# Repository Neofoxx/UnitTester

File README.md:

# UnitTester
A rack mounted piece of gear for testing chips

#### Why
Always wanted some rack-mount piece of gear based on the DIN 41612 standard. This is slightly modified.
Also, want to test the complete PIC32 toolchain without plugging and replugging the programmer a thousand times.

#### When
Soon.

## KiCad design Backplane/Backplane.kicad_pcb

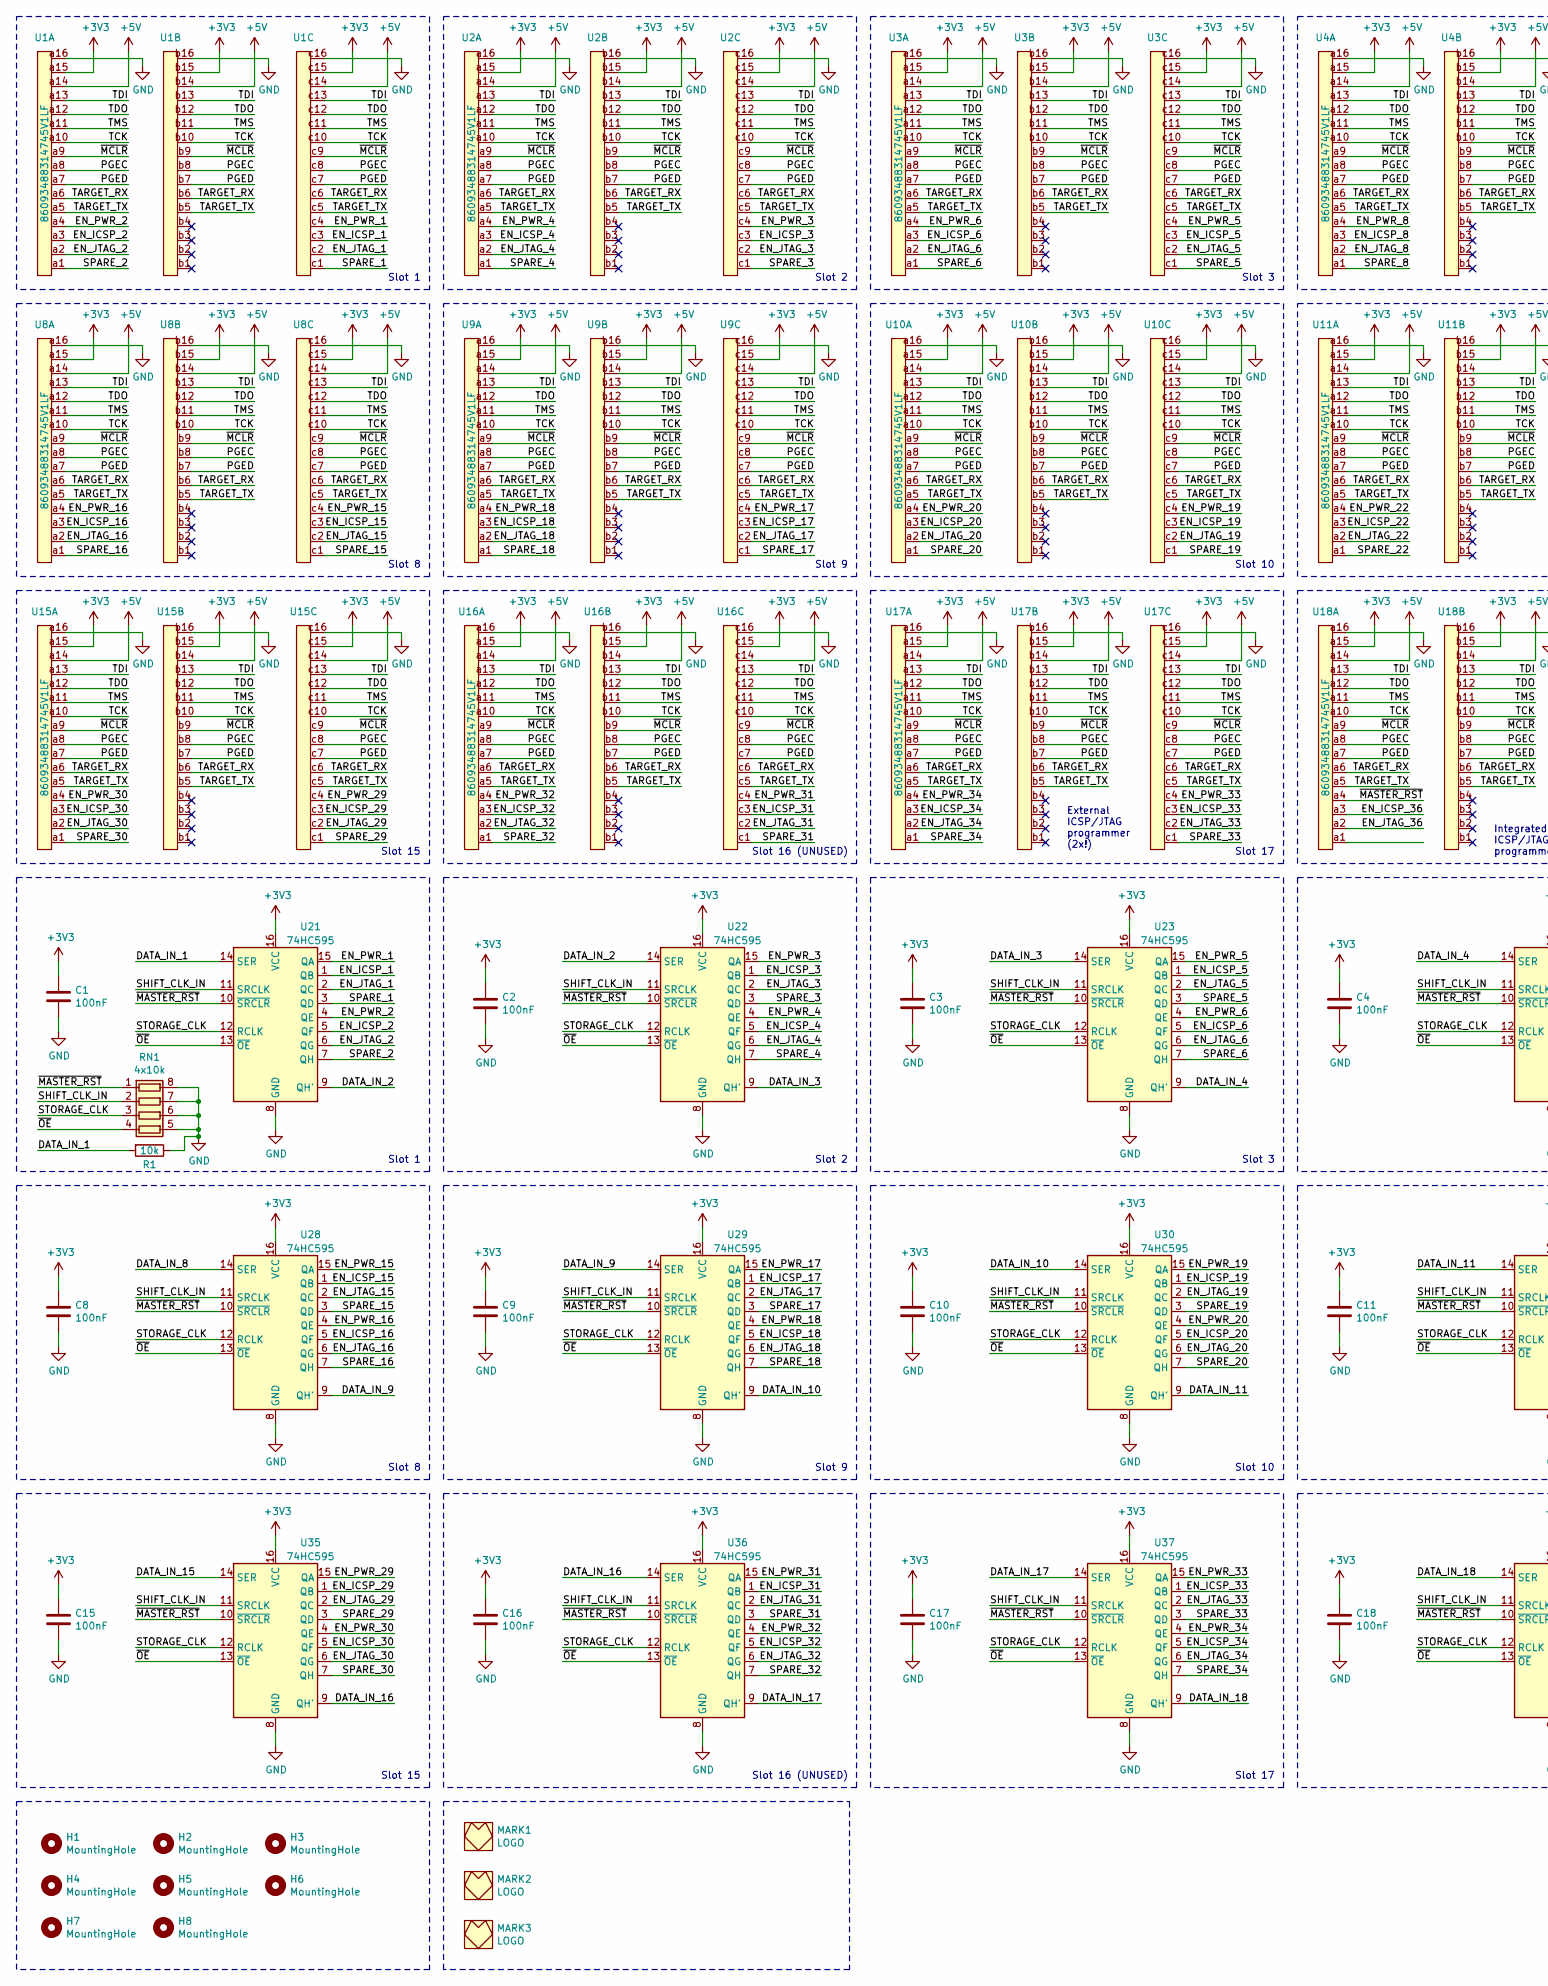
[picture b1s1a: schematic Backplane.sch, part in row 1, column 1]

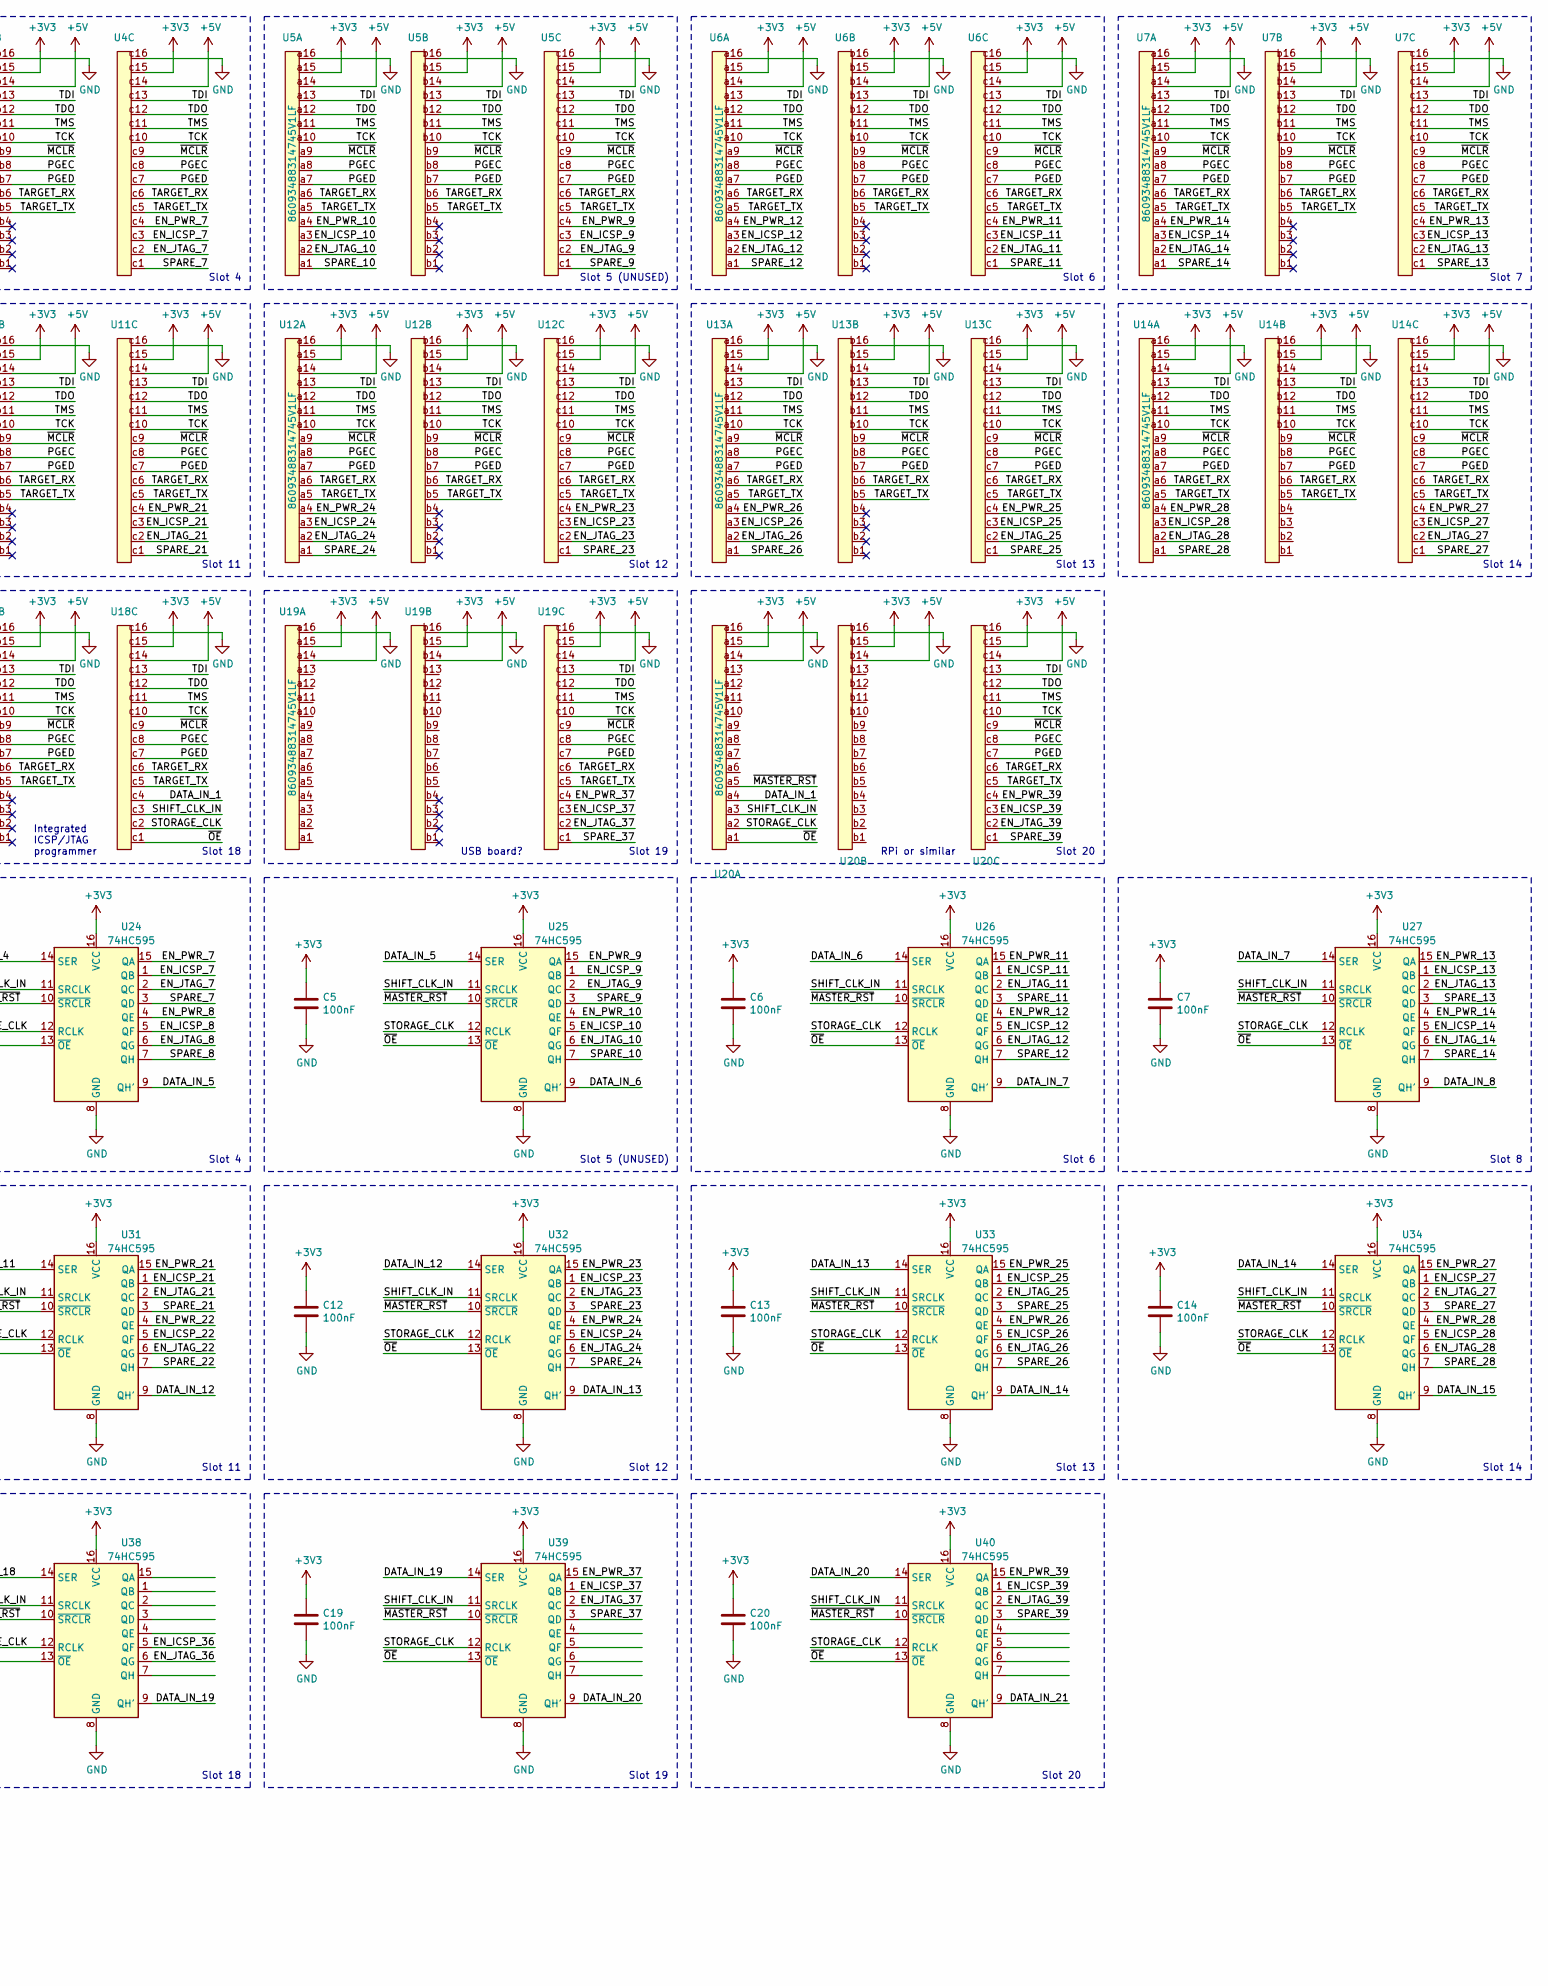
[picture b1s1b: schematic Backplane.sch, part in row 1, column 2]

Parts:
C1, C2, C3, C4, C5, C6, C7, C8, C9, C10, C11, C12, C13, C14, C15, C16, C17, C18, C19, C20: 100nF; C_0603_1608Metric_Pad1.08x0.95mm_HandSolder
H1, H2, H3, H4, H5, H6, H7, H8: MountingHole; MountingHole_3.2mm_M3
MARK1: LOGO; FOX_LOGO_COPPER
MARK2: LOGO; FOX_LOGO_MASK
MARK3: LOGO; FOX_LOGO_SILK
R1: 10k; R_0603_1608Metric_Pad0.98x0.95mm_HandSolder
RN1: 4x10k; R_Array_Convex_4x0603
U1, U2, U3, U4, U5, U6, U7, U8, U9, U10, U11, U12, U13, U14, U15, U16, U17, U18, U19, U20: 86093488314745V1LF; DIN41612_C2_3x16_Female_Vertical_THT; Mouser 649-869348314745V1LF
U21, U22, U23, U24, U25, U26, U27, U28, U29, U30, U31, U32, U33, U34, U35, U36, U37, U38, U39, U40: 74HC595; TSSOP-16_4.4x5mm_P0.65mm

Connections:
+3V3: C1.1, C2.1, C3.1, C4.1, C5.1, C6.1, C7.1, C8.1, C9.1, C10.1, C11.1, C12.1, C13.1, C14.1, C15.1, C16.1, C17.1, C18.1, C19.1, C20.1, U1.a15, U1.b15, U1.c15, U2.a15, U2.b15, U2.c15, U3.a15, U3.b15, U3.c15, U4.a15, U4.b15, U4.c15, U5.a15, U5.b15, U5.c15, U6.a15, U6.b15, U6.c15, U7.a15, U7.b15, U7.c15, U8.a15, U8.b15, U8.c15, U9.a15, U9.b15, U9.c15, U10.a15, U10.b15, U10.c15, U11.a15, U11.b15, U11.c15, U12.a15, U12.b15, U12.c15, U13.a15, U13.b15, U13.c15, U14.a15, U14.b15, U14.c15, U15.a15, U15.b15, U15.c15, U16.a15, U16.b15, U16.c15, U17.a15, U17.b15, U17.c15, U18.a15, U18.b15, U18.c15, U19.a15, U19.b15, U19.c15, U20.a15, U20.b15, U20.c15, U21.16 (VCC), U22.16 (VCC), U23.16 (VCC), U24.16 (VCC), U25.16 (VCC), U26.16 (VCC), U27.16 (VCC), U28.16 (VCC), U29.16 (VCC), U30.16 (VCC), U31.16 (VCC), U32.16 (VCC), U33.16 (VCC), U34.16 (VCC), U35.16 (VCC), U36.16 (VCC), U37.16 (VCC), U38.16 (VCC), U39.16 (VCC), U40.16 (VCC)
+5V: U1.a14, U1.b14, U1.c14, U2.a14, U2.b14, U2.c14, U3.a14, U3.b14, U3.c14, U4.a14, U4.b14, U4.c14, U5.a14, U5.b14, U5.c14, U6.a14, U6.b14, U6.c14, U7.a14, U7.b14, U7.c14, U8.a14, U8.b14, U8.c14, U9.a14, U9.b14, U9.c14, U10.a14, U10.b14, U10.c14, U11.a14, U11.b14, U11.c14, U12.a14, U12.b14, U12.c14, U13.a14, U13.b14, U13.c14, U14.a14, U14.b14, U14.c14, U15.a14, U15.b14, U15.c14, U16.a14, U16.b14, U16.c14, U17.a14, U17.b14, U17.c14, U18.a14, U18.b14, U18.c14, U19.a14, U19.b14, U19.c14, U20.a14, U20.b14, U20.c14
/DATA_IN_1: R1.2, U18.c4, U20.a4, U21.14 (SER)
/DATA_IN_2: U21.9 (QH'), U22.14 (SER)
/DATA_IN_3: U22.9 (QH'), U23.14 (SER)
/DATA_IN_4: U23.9 (QH'), U24.14 (SER)
/DATA_IN_5: U24.9 (QH'), U25.14 (SER)
/DATA_IN_6: U25.9 (QH'), U26.14 (SER)
/DATA_IN_7: U26.9 (QH'), U27.14 (SER)
/DATA_IN_8: U27.9 (QH'), U28.14 (SER)
/DATA_IN_9: U28.9 (QH'), U29.14 (SER)
/DATA_IN_10: U29.9 (QH'), U30.14 (SER)
/DATA_IN_11: U30.9 (QH'), U31.14 (SER)
/DATA_IN_12: U31.9 (QH'), U32.14 (SER)
/DATA_IN_13: U32.9 (QH'), U33.14 (SER)
/DATA_IN_14: U33.9 (QH'), U34.14 (SER)
/DATA_IN_15: U34.9 (QH'), U35.14 (SER)
/DATA_IN_16: U35.9 (QH'), U36.14 (SER)
/DATA_IN_17: U36.9 (QH'), U37.14 (SER)
/DATA_IN_18: U37.9 (QH'), U38.14 (SER)
/DATA_IN_19: U38.9 (QH'), U39.14 (SER)
/DATA_IN_20: U39.9 (QH'), U40.14 (SER)
/EN_ICSP_1: U1.c3, U21.1 (QB)
/EN_ICSP_2: U1.a3, U21.5 (QF)
/EN_ICSP_3: U2.c3, U22.1 (QB)
/EN_ICSP_4: U2.a3, U22.5 (QF)
/EN_ICSP_5: U3.c3, U23.1 (QB)
/EN_ICSP_6: U3.a3, U23.5 (QF)
/EN_ICSP_7: U4.c3, U24.1 (QB)
/EN_ICSP_8: U4.a3, U24.5 (QF)
/EN_ICSP_9: U5.c3, U25.1 (QB)
/EN_ICSP_10: U5.a3, U25.5 (QF)
/EN_ICSP_11: U6.c3, U26.1 (QB)
/EN_ICSP_12: U6.a3, U26.5 (QF)
/EN_ICSP_13: U7.c3, U27.1 (QB)
/EN_ICSP_14: U7.a3, U27.5 (QF)
/EN_ICSP_15: U8.c3, U28.1 (QB)
/EN_ICSP_16: U8.a3, U28.5 (QF)
/EN_ICSP_17: U9.c3, U29.1 (QB)
/EN_ICSP_18: U9.a3, U29.5 (QF)
/EN_ICSP_19: U10.c3, U30.1 (QB)
/EN_ICSP_20: U10.a3, U30.5 (QF)
/EN_ICSP_21: U11.c3, U31.1 (QB)
/EN_ICSP_22: U11.a3, U31.5 (QF)
/EN_ICSP_23: U12.c3, U32.1 (QB)
/EN_ICSP_24: U12.a3, U32.5 (QF)
/EN_ICSP_25: U13.c3, U33.1 (QB)
/EN_ICSP_26: U13.a3, U33.5 (QF)
/EN_ICSP_27: U14.c3, U34.1 (QB)
/EN_ICSP_28: U14.a3, U34.5 (QF)
/EN_ICSP_29: U15.c3, U35.1 (QB)
/EN_ICSP_30: U15.a3, U35.5 (QF)
/EN_ICSP_31: U16.c3, U36.1 (QB)
/EN_ICSP_32: U16.a3, U36.5 (QF)
/EN_ICSP_33: U17.c3, U37.1 (QB)
/EN_ICSP_34: U17.a3, U37.5 (QF)
/EN_ICSP_36: U18.a3, U38.5 (QF)
/EN_ICSP_37: U19.c3, U39.1 (QB)
/EN_ICSP_39: U20.c3, U40.1 (QB)
/EN_JTAG_1: U1.c2, U21.2 (QC)
/EN_JTAG_2: U1.a2, U21.6 (QG)
/EN_JTAG_3: U2.c2, U22.2 (QC)
/EN_JTAG_4: U2.a2, U22.6 (QG)
/EN_JTAG_5: U3.c2, U23.2 (QC)
/EN_JTAG_6: U3.a2, U23.6 (QG)
/EN_JTAG_7: U4.c2, U24.2 (QC)
/EN_JTAG_8: U4.a2, U24.6 (QG)
/EN_JTAG_9: U5.c2, U25.2 (QC)
/EN_JTAG_10: U5.a2, U25.6 (QG)
/EN_JTAG_11: U6.c2, U26.2 (QC)
/EN_JTAG_12: U6.a2, U26.6 (QG)
/EN_JTAG_13: U7.c2, U27.2 (QC)
/EN_JTAG_14: U7.a2, U27.6 (QG)
/EN_JTAG_15: U8.c2, U28.2 (QC)
/EN_JTAG_16: U8.a2, U28.6 (QG)
/EN_JTAG_17: U9.c2, U29.2 (QC)
/EN_JTAG_18: U9.a2, U29.6 (QG)
/EN_JTAG_19: U10.c2, U30.2 (QC)
/EN_JTAG_20: U10.a2, U30.6 (QG)
/EN_JTAG_21: U11.c2, U31.2 (QC)
/EN_JTAG_22: U11.a2, U31.6 (QG)
/EN_JTAG_23: U12.c2, U32.2 (QC)
/EN_JTAG_24: U12.a2, U32.6 (QG)
/EN_JTAG_25: U13.c2, U33.2 (QC)
/EN_JTAG_26: U13.a2, U33.6 (QG)
/EN_JTAG_27: U14.c2, U34.2 (QC)
/EN_JTAG_28: U14.a2, U34.6 (QG)
/EN_JTAG_29: U15.c2, U35.2 (QC)
/EN_JTAG_30: U15.a2, U35.6 (QG)
/EN_JTAG_31: U16.c2, U36.2 (QC)
/EN_JTAG_32: U16.a2, U36.6 (QG)
/EN_JTAG_33: U17.c2, U37.2 (QC)
/EN_JTAG_34: U17.a2, U37.6 (QG)
/EN_JTAG_36: U18.a2, U38.6 (QG)
/EN_JTAG_37: U19.c2, U39.2 (QC)
/EN_JTAG_39: U20.c2, U40.2 (QC)
/EN_PWR_1: U1.c4, U21.15 (QA)
/EN_PWR_2: U1.a4, U21.4 (QE)
/EN_PWR_3: U2.c4, U22.15 (QA)
/EN_PWR_4: U2.a4, U22.4 (QE)
/EN_PWR_5: U3.c4, U23.15 (QA)
/EN_PWR_6: U3.a4, U23.4 (QE)
/EN_PWR_7: U4.c4, U24.15 (QA)
/EN_PWR_8: U4.a4, U24.4 (QE)
/EN_PWR_9: U5.c4, U25.15 (QA)
/EN_PWR_10: U5.a4, U25.4 (QE)
/EN_PWR_11: U6.c4, U26.15 (QA)
/EN_PWR_12: U6.a4, U26.4 (QE)
/EN_PWR_13: U7.c4, U27.15 (QA)
/EN_PWR_14: U7.a4, U27.4 (QE)
/EN_PWR_15: U8.c4, U28.15 (QA)
/EN_PWR_16: U8.a4, U28.4 (QE)
/EN_PWR_17: U9.c4, U29.15 (QA)
/EN_PWR_18: U9.a4, U29.4 (QE)
/EN_PWR_19: U10.c4, U30.15 (QA)
/EN_PWR_20: U10.a4, U30.4 (QE)
/EN_PWR_21: U11.c4, U31.15 (QA)
/EN_PWR_22: U11.a4, U31.4 (QE)
/EN_PWR_23: U12.c4, U32.15 (QA)
/EN_PWR_24: U12.a4, U32.4 (QE)
/EN_PWR_25: U13.c4, U33.15 (QA)
/EN_PWR_26: U13.a4, U33.4 (QE)
/EN_PWR_27: U14.c4, U34.15 (QA)
/EN_PWR_28: U14.a4, U34.4 (QE)
/EN_PWR_29: U15.c4, U35.15 (QA)
/EN_PWR_30: U15.a4, U35.4 (QE)
/EN_PWR_31: U16.c4, U36.15 (QA)
/EN_PWR_32: U16.a4, U36.4 (QE)
/EN_PWR_33: U17.c4, U37.15 (QA)
/EN_PWR_34: U17.a4, U37.4 (QE)
/EN_PWR_37: U19.c4, U39.15 (QA)
/EN_PWR_39: U20.c4, U40.15 (QA)
/PGEC: U1.a8, U1.b8, U1.c8, U2.a8, U2.b8, U2.c8, U3.a8, U3.b8, U3.c8, U4.a8, U4.b8, U4.c8, U5.a8, U5.b8, U5.c8, U6.a8, U6.b8, U6.c8, U7.a8, U7.b8, U7.c8, U8.a8, U8.b8, U8.c8, U9.a8, U9.b8, U9.c8, U10.a8, U10.b8, U10.c8, U11.a8, U11.b8, U11.c8, U12.a8, U12.b8, U12.c8, U13.a8, U13.b8, U13.c8, U14.a8, U14.b8, U14.c8, U15.a8, U15.b8, U15.c8, U16.a8, U16.b8, U16.c8, U17.a8, U17.b8, U17.c8, U18.a8, U18.b8, U18.c8, U19.c8, U20.c8
/PGED: U1.a7, U1.b7, U1.c7, U2.a7, U2.b7, U2.c7, U3.a7, U3.b7, U3.c7, U4.a7, U4.b7, U4.c7, U5.a7, U5.b7, U5.c7, U6.a7, U6.b7, U6.c7, U7.a7, U7.b7, U7.c7, U8.a7, U8.b7, U8.c7, U9.a7, U9.b7, U9.c7, U10.a7, U10.b7, U10.c7, U11.a7, U11.b7, U11.c7, U12.a7, U12.b7, U12.c7, U13.a7, U13.b7, U13.c7, U14.a7, U14.b7, U14.c7, U15.a7, U15.b7, U15.c7, U16.a7, U16.b7, U16.c7, U17.a7, U17.b7, U17.c7, U18.a7, U18.b7, U18.c7, U19.c7, U20.c7
/SHIFT_CLK_IN: RN1.2 (R2.1), U18.c3, U20.a3, U21.11 (SRCLK), U22.11 (SRCLK), U23.11 (SRCLK), U24.11 (SRCLK), U25.11 (SRCLK), U26.11 (SRCLK), U27.11 (SRCLK), U28.11 (SRCLK), U29.11 (SRCLK), U30.11 (SRCLK), U31.11 (SRCLK), U32.11 (SRCLK), U33.11 (SRCLK), U34.11 (SRCLK), U35.11 (SRCLK), U36.11 (SRCLK), U37.11 (SRCLK), U38.11 (SRCLK), U39.11 (SRCLK), U40.11 (SRCLK)
/SPARE_1: U1.c1, U21.3 (QD)
/SPARE_2: U1.a1, U21.7 (QH)
/SPARE_3: U2.c1, U22.3 (QD)
/SPARE_4: U2.a1, U22.7 (QH)
/SPARE_5: U3.c1, U23.3 (QD)
/SPARE_6: U3.a1, U23.7 (QH)
/SPARE_7: U4.c1, U24.3 (QD)
/SPARE_8: U4.a1, U24.7 (QH)
/SPARE_9: U5.c1, U25.3 (QD)
/SPARE_10: U5.a1, U25.7 (QH)
/SPARE_11: U6.c1, U26.3 (QD)
/SPARE_12: U6.a1, U26.7 (QH)
/SPARE_13: U7.c1, U27.3 (QD)
/SPARE_14: U7.a1, U27.7 (QH)
/SPARE_15: U8.c1, U28.3 (QD)
/SPARE_16: U8.a1, U28.7 (QH)
/SPARE_17: U9.c1, U29.3 (QD)
/SPARE_18: U9.a1, U29.7 (QH)
/SPARE_19: U10.c1, U30.3 (QD)
/SPARE_20: U10.a1, U30.7 (QH)
/SPARE_21: U11.c1, U31.3 (QD)
/SPARE_22: U11.a1, U31.7 (QH)
/SPARE_23: U12.c1, U32.3 (QD)
/SPARE_24: U12.a1, U32.7 (QH)
/SPARE_25: U13.c1, U33.3 (QD)
/SPARE_26: U13.a1, U33.7 (QH)
/SPARE_27: U14.c1, U34.3 (QD)
/SPARE_28: U14.a1, U34.7 (QH)
/SPARE_29: U15.c1, U35.3 (QD)
/SPARE_30: U15.a1, U35.7 (QH)
/SPARE_31: U16.c1, U36.3 (QD)
/SPARE_32: U16.a1, U36.7 (QH)
/SPARE_33: U17.c1, U37.3 (QD)
/SPARE_34: U17.a1, U37.7 (QH)
/SPARE_37: U19.c1, U39.3 (QD)
/SPARE_39: U20.c1, U40.3 (QD)
/STORAGE_CLK: RN1.3 (R3.1), U18.c2, U20.a2, U21.12 (RCLK), U22.12 (RCLK), U23.12 (RCLK), U24.12 (RCLK), U25.12 (RCLK), U26.12 (RCLK), U27.12 (RCLK), U28.12 (RCLK), U29.12 (RCLK), U30.12 (RCLK), U31.12 (RCLK), U32.12 (RCLK), U33.12 (RCLK), U34.12 (RCLK), U35.12 (RCLK), U36.12 (RCLK), U37.12 (RCLK), U38.12 (RCLK), U39.12 (RCLK), U40.12 (RCLK)
/TARGET_RX: U1.a6, U1.b6, U1.c6, U2.a6, U2.b6, U2.c6, U3.a6, U3.b6, U3.c6, U4.a6, U4.b6, U4.c6, U5.a6, U5.b6, U5.c6, U6.a6, U6.b6, U6.c6, U7.a6, U7.b6, U7.c6, U8.a6, U8.b6, U8.c6, U9.a6, U9.b6, U9.c6, U10.a6, U10.b6, U10.c6, U11.a6, U11.b6, U11.c6, U12.a6, U12.b6, U12.c6, U13.a6, U13.b6, U13.c6, U14.a6, U14.b6, U14.c6, U15.a6, U15.b6, U15.c6, U16.a6, U16.b6, U16.c6, U17.a6, U17.b6, U17.c6, U18.a6, U18.b6, U18.c6, U19.c6, U20.c6
/TARGET_TX: U1.a5, U1.b5, U1.c5, U2.a5, U2.b5, U2.c5, U3.a5, U3.b5, U3.c5, U4.a5, U4.b5, U4.c5, U5.a5, U5.b5, U5.c5, U6.a5, U6.b5, U6.c5, U7.a5, U7.b5, U7.c5, U8.a5, U8.b5, U8.c5, U9.a5, U9.b5, U9.c5, U10.a5, U10.b5, U10.c5, U11.a5, U11.b5, U11.c5, U12.a5, U12.b5, U12.c5, U13.a5, U13.b5, U13.c5, U14.a5, U14.b5, U14.c5, U15.a5, U15.b5, U15.c5, U16.a5, U16.b5, U16.c5, U17.a5, U17.b5, U17.c5, U18.a5, U18.b5, U18.c5, U19.c5, U20.c5
/TCK: U1.a10, U1.b10, U1.c10, U2.a10, U2.b10, U2.c10, U3.a10, U3.b10, U3.c10, U4.a10, U4.b10, U4.c10, U5.a10, U5.b10, U5.c10, U6.a10, U6.b10, U6.c10, U7.a10, U7.b10, U7.c10, U8.a10, U8.b10, U8.c10, U9.a10, U9.b10, U9.c10, U10.a10, U10.b10, U10.c10, U11.a10, U11.b10, U11.c10, U12.a10, U12.b10, U12.c10, U13.a10, U13.b10, U13.c10, U14.a10, U14.b10, U14.c10, U15.a10, U15.b10, U15.c10, U16.a10, U16.b10, U16.c10, U17.a10, U17.b10, U17.c10, U18.a10, U18.b10, U18.c10, U19.c10, U20.c10
/TDI: U1.a13, U1.b13, U1.c13, U2.a13, U2.b13, U2.c13, U3.a13, U3.b13, U3.c13, U4.a13, U4.b13, U4.c13, U5.a13, U5.b13, U5.c13, U6.a13, U6.b13, U6.c13, U7.a13, U7.b13, U7.c13, U8.a13, U8.b13, U8.c13, U9.a13, U9.b13, U9.c13, U10.a13, U10.b13, U10.c13, U11.a13, U11.b13, U11.c13, U12.a13, U12.b13, U12.c13, U13.a13, U13.b13, U13.c13, U14.a13, U14.b13, U14.c13, U15.a13, U15.b13, U15.c13, U16.a13, U16.b13, U16.c13, U17.a13, U17.b13, U17.c13, U18.a13, U18.b13, U18.c13, U19.c13, U20.c13
/TDO: U1.a12, U1.b12, U1.c12, U2.a12, U2.b12, U2.c12, U3.a12, U3.b12, U3.c12, U4.a12, U4.b12, U4.c12, U5.a12, U5.b12, U5.c12, U6.a12, U6.b12, U6.c12, U7.a12, U7.b12, U7.c12, U8.a12, U8.b12, U8.c12, U9.a12, U9.b12, U9.c12, U10.a12, U10.b12, U10.c12, U11.a12, U11.b12, U11.c12, U12.a12, U12.b12, U12.c12, U13.a12, U13.b12, U13.c12, U14.a12, U14.b12, U14.c12, U15.a12, U15.b12, U15.c12, U16.a12, U16.b12, U16.c12, U17.a12, U17.b12, U17.c12, U18.a12, U18.b12, U18.c12, U19.c12, U20.c12
/TMS: U1.a11, U1.b11, U1.c11, U2.a11, U2.b11, U2.c11, U3.a11, U3.b11, U3.c11, U4.a11, U4.b11, U4.c11, U5.a11, U5.b11, U5.c11, U6.a11, U6.b11, U6.c11, U7.a11, U7.b11, U7.c11, U8.a11, U8.b11, U8.c11, U9.a11, U9.b11, U9.c11, U10.a11, U10.b11, U10.c11, U11.a11, U11.b11, U11.c11, U12.a11, U12.b11, U12.c11, U13.a11, U13.b11, U13.c11, U14.a11, U14.b11, U14.c11, U15.a11, U15.b11, U15.c11, U16.a11, U16.b11, U16.c11, U17.a11, U17.b11, U17.c11, U18.a11, U18.b11, U18.c11, U19.c11, U20.c11
/~MASTER_RST: RN1.1 (R1.1), U18.a4, U20.a5, U21.10 (~SRCLR), U22.10 (~SRCLR), U23.10 (~SRCLR), U24.10 (~SRCLR), U25.10 (~SRCLR), U26.10 (~SRCLR), U27.10 (~SRCLR), U28.10 (~SRCLR), U29.10 (~SRCLR), U30.10 (~SRCLR), U31.10 (~SRCLR), U32.10 (~SRCLR), U33.10 (~SRCLR), U34.10 (~SRCLR), U35.10 (~SRCLR), U36.10 (~SRCLR), U37.10 (~SRCLR), U38.10 (~SRCLR), U39.10 (~SRCLR), U40.10 (~SRCLR)
/~MCLR: U1.a9, U1.b9, U1.c9, U2.a9, U2.b9, U2.c9, U3.a9, U3.b9, U3.c9, U4.a9, U4.b9, U4.c9, U5.a9, U5.b9, U5.c9, U6.a9, U6.b9, U6.c9, U7.a9, U7.b9, U7.c9, U8.a9, U8.b9, U8.c9, U9.a9, U9.b9, U9.c9, U10.a9, U10.b9, U10.c9, U11.a9, U11.b9, U11.c9, U12.a9, U12.b9, U12.c9, U13.a9, U13.b9, U13.c9, U14.a9, U14.b9, U14.c9, U15.a9, U15.b9, U15.c9, U16.a9, U16.b9, U16.c9, U17.a9, U17.b9, U17.c9, U18.a9, U18.b9, U18.c9, U19.c9, U20.c9
/~OE: RN1.4 (R4.1), U18.c1, U20.a1, U21.13 (~OE), U22.13 (~OE), U23.13 (~OE), U24.13 (~OE), U25.13 (~OE), U26.13 (~OE), U27.13 (~OE), U28.13 (~OE), U29.13 (~OE), U30.13 (~OE), U31.13 (~OE), U32.13 (~OE), U33.13 (~OE), U34.13 (~OE), U35.13 (~OE), U36.13 (~OE), U37.13 (~OE), U38.13 (~OE), U39.13 (~OE), U40.13 (~OE)
GND: C1.2, C2.2, C3.2, C4.2, C5.2, C6.2, C7.2, C8.2, C9.2, C10.2, C11.2, C12.2, C13.2, C14.2, C15.2, C16.2, C17.2, C18.2, C19.2, C20.2, R1.1, RN1.5 (R4.2), RN1.6 (R3.2), RN1.7 (R2.2), RN1.8 (R1.2), U1.a16, U1.b16, U1.c16, U2.a16, U2.b16, U2.c16, U3.a16, U3.b16, U3.c16, U4.a16, U4.b16, U4.c16, U5.a16, U5.b16, U5.c16, U6.a16, U6.b16, U6.c16, U7.a16, U7.b16, U7.c16, U8.a16, U8.b16, U8.c16, U9.a16, U9.b16, U9.c16, U10.a16, U10.b16, U10.c16, U11.a16, U11.b16, U11.c16, U12.a16, U12.b16, U12.c16, U13.a16, U13.b16, U13.c16, U14.a16, U14.b16, U14.c16, U15.a16, U15.b16, U15.c16, U16.a16, U16.b16, U16.c16, U17.a16, U17.b16, U17.c16, U18.a16, U18.b16, U18.c16, U19.a16, U19.b16, U19.c16, U20.a16, U20.b16, U20.c16, U21.8 (GND), U22.8 (GND), U23.8 (GND), U24.8 (GND), U25.8 (GND), U26.8 (GND), U27.8 (GND), U28.8 (GND), U29.8 (GND), U30.8 (GND), U31.8 (GND), U32.8 (GND), U33.8 (GND), U34.8 (GND), U35.8 (GND), U36.8 (GND), U37.8 (GND), U38.8 (GND), U39.8 (GND), U40.8 (GND)

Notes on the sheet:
Slot 1
Slot 2
Slot 3
Slot 4
Slot 5 (UNUSED)
Slot 6
Slot 7
Slot 8
Slot 9
Slot 10
Slot 11
Slot 12
Slot 13
Slot 14
Slot 15
Slot 16 (UNUSED)
Slot 17
Slot 18
Slot 19
Slot 20
RPi or similar
USB board?
Integrated ICSP/JTAG programmer
External ICSP/JTAG programmer (2x!)

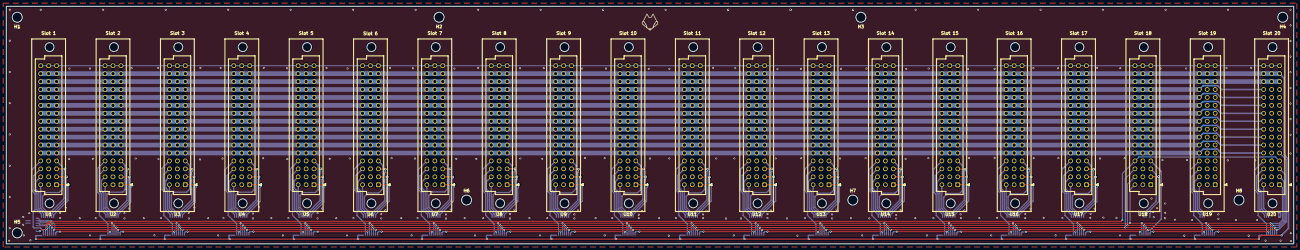
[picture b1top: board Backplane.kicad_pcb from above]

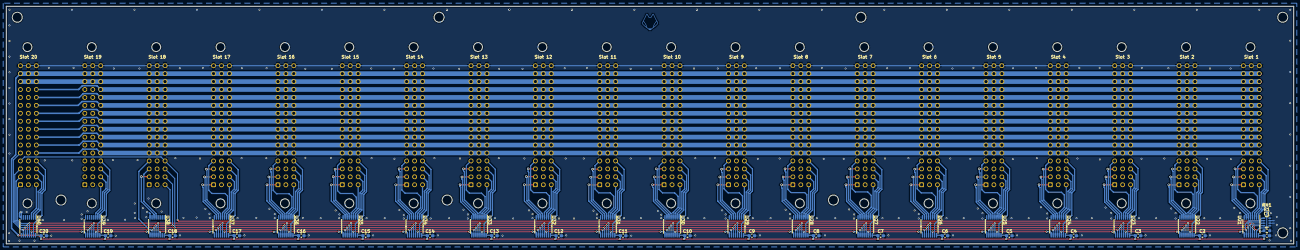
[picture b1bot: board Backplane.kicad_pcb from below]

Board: 2 copper layers, 412.0 x 76.0 mm, 73 parts (45 on the bottom side), 182 nets.

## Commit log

2021-11-29 Belated start
2021-11-29 Rotate all connectors on the backplane (measure twice...)
2021-11-30 Mid-work commit. Add README
2021-12-05 mid-work commit, preparing the riser card
2021-12-05 Mid-work commit. IT's not pretty but it'll work
2022-01-02 Mid-work commit. Added notes, figured out what works, etc.
2022-01-09 Added comparison of chips, etc.
2022-01-09 Move and rename
2022-01-09 Add Rev2 of Riser Card. LED connection fixed.
2022-05-29 Move from one computer to another, commit changes
2022-05-29 Updte current status
2022-07-05 Update current status
2022-11-17 Update to latest state on primary computer
